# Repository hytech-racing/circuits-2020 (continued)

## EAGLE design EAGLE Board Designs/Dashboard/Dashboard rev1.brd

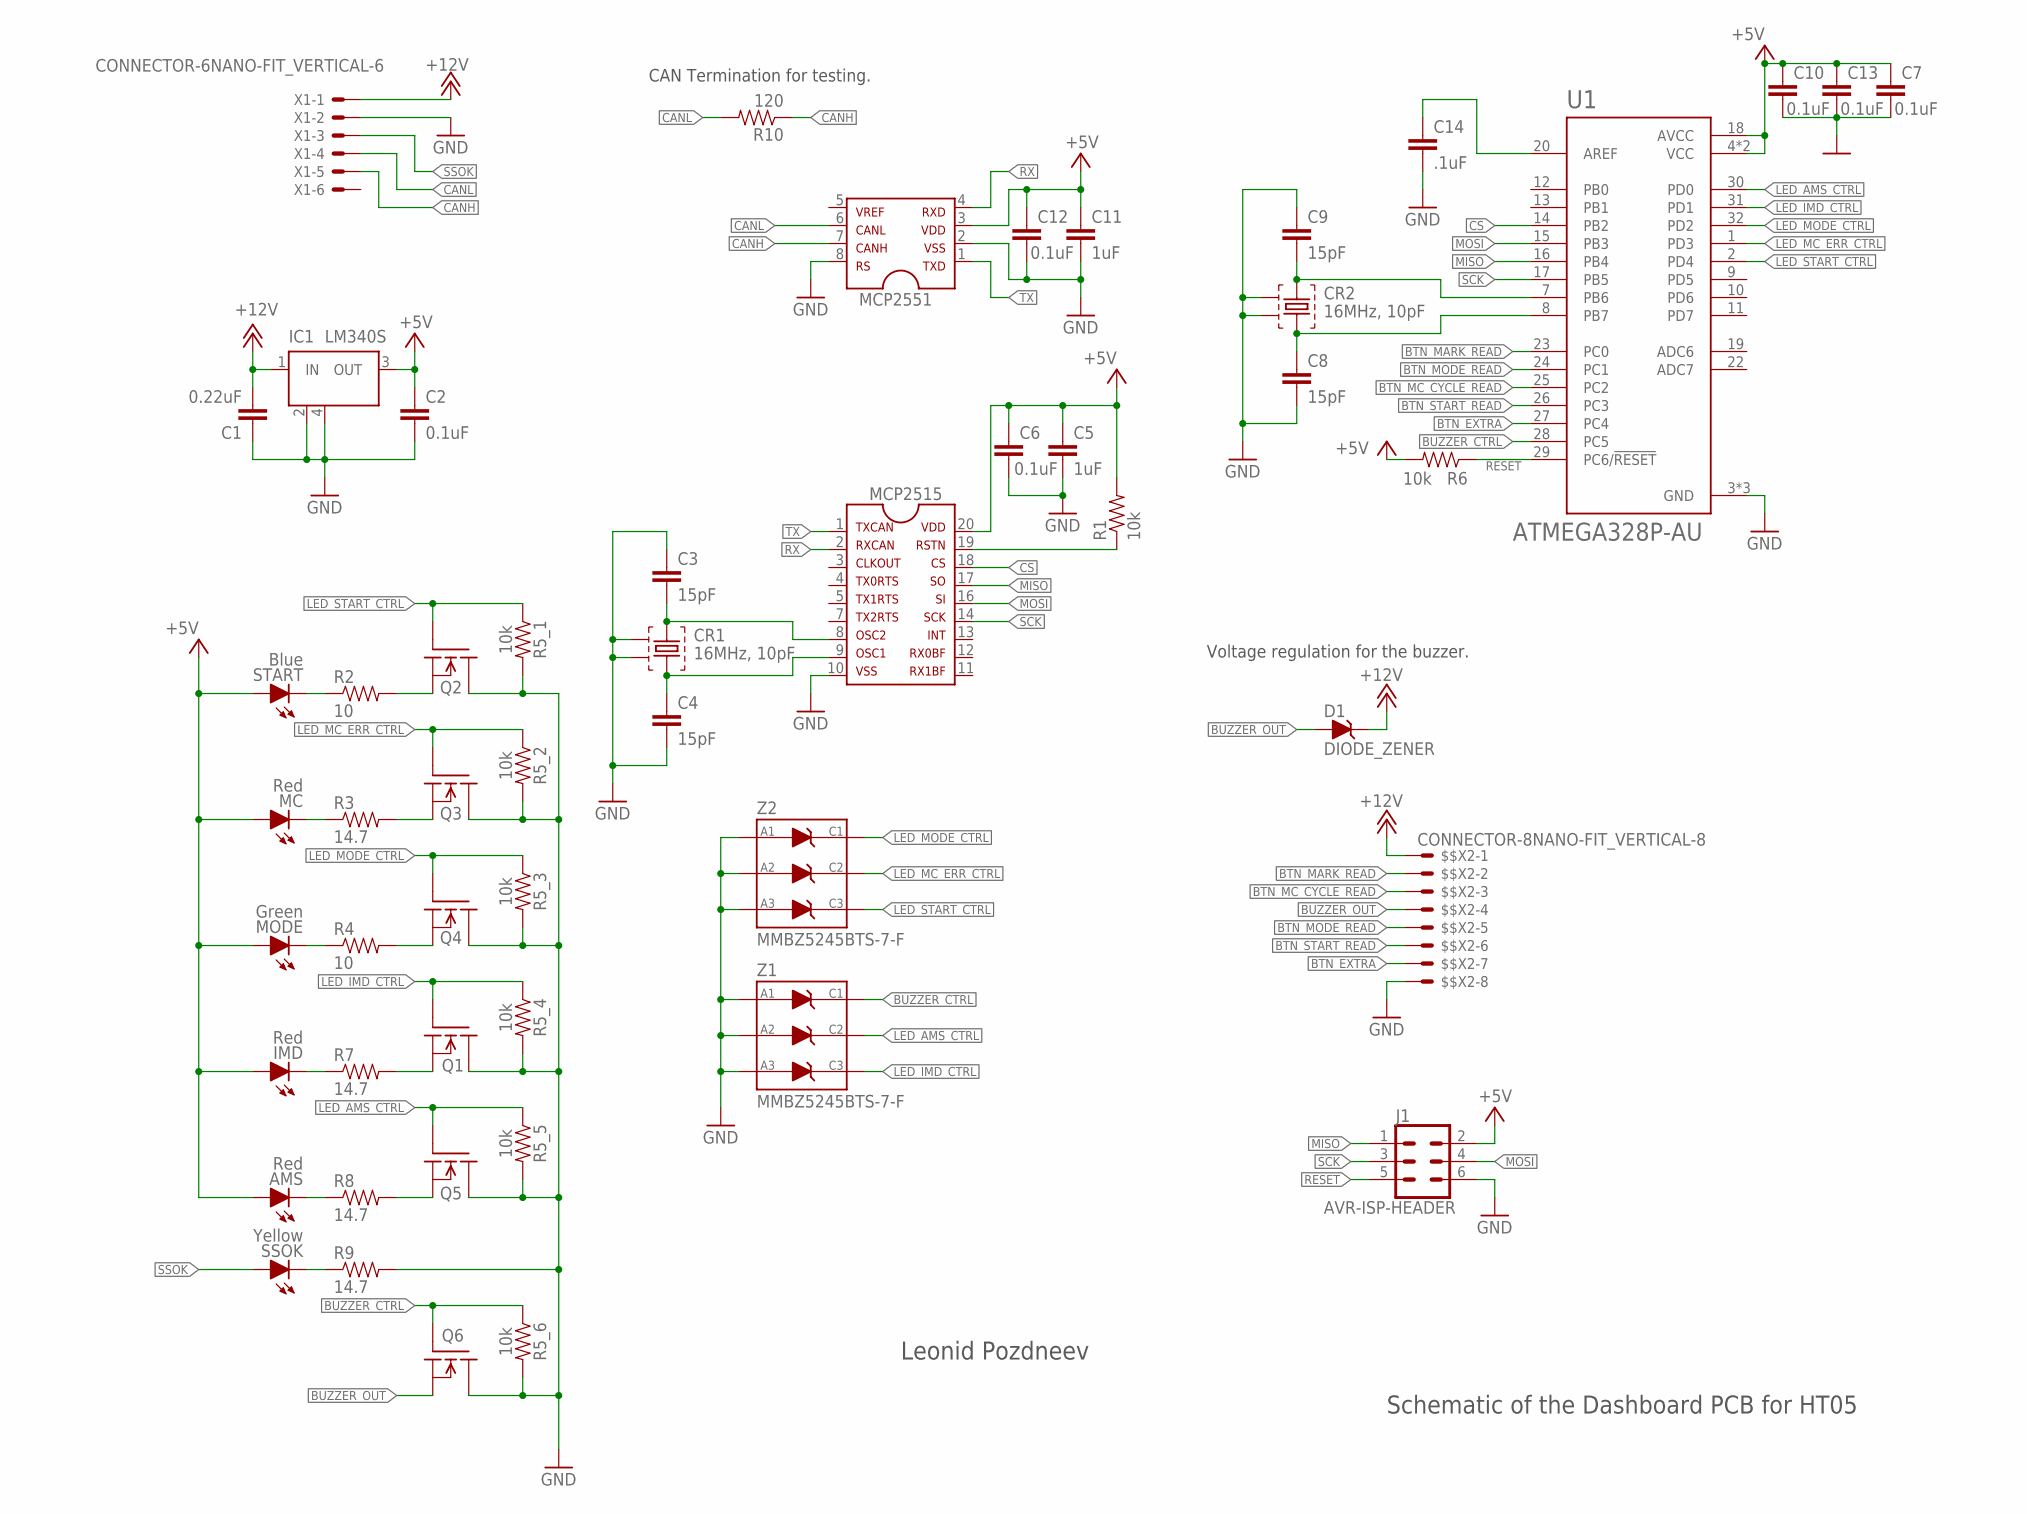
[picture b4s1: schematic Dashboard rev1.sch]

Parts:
$$X2: CONNECTOR-8NANO-FIT_VERTICAL-8; NANO-FIT_VERTICAL-8
AMS: Red; CREE_XP-E2
C1: 0.22uF; 0603-CAP
C2, C6, C7, C10, C12, C13: 0.1uF; 0603-CAP
C3, C4, C8, C9: 15pF; 0603-CAP
C5, C11: 1uF; 0603-CAP
C14: .1uF; 0603-CAP
CR1, CR2: 16MHz, 10pF; ABM3B
D1: DIODE_ZENER; SOT23
IC1: LM340S; SOT223
IMD: Red; CREE_XP-E2
J1: AVR-ISP-HEADER; 2X03
MC: Red; CREE_XP-E2
MCP2515: MCP2515TSSOP; TSSOP-20
MCP2551: MCP2551; SOIC-08
MODE: Green; CREE_XP-E2
Q1, Q2, Q3, Q4, Q5, Q6: DMG3406LSOT; SOT23
R1, R6: 10k; 0603-RES
R2, R4: 10; 0603-RES
R3, R7, R8, R9: 14.7; 0603-RES
R5: 10k; CAT16-*8
R10: 120; 0603-RES
SSOK: Yellow; CREE_XP-E2
START: Blue; CREE_XP-E2
U1: ATMEGA328P-AU; QFP80P900X900X120-32N
X1: CONNECTOR-6NANO-FIT_VERTICAL-6; NANO-FIT_VERTICAL-6
Z1, Z2: MMBZ5245BTS-7-F; SOT363

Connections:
+5V: AMS.P$1 (A), C2.1, C5.1, C6.1, C7.1, C10.1, C11.1, C12.1, C13.1, IC1.3 (OUT), IMD.P$1 (A), J1.2, MC.P$1 (A), MCP2515.20 (VDD), MCP2551.3, MODE.P$1 (A), R1.2, R6.2, START.P$1 (A), U1.4 (VCC), U1.6 (VCC), U1.18 (AVCC)
+12V: $$X2.P$1, C1.2, D1.3 (C), IC1.1 (IN), X1.P$1
BTN_EXTRA: $$X2.P$7, U1.27 (PC4)
BTN_MARK_READ: $$X2.P$2, U1.23 (PC0)
BTN_MC_CYCLE_READ: $$X2.P$3, U1.25 (PC2)
BTN_MODE_READ: $$X2.P$5, U1.24 (PC1)
BTN_START_READ: $$X2.P$6, U1.26 (PC3)
BUZZER_CTRL: Q6.1 (G), R5.P$6 (1), U1.28 (PC5), Z1.P$4 (C1)
BUZZER_OUT: $$X2.P$4, D1.1 (A), Q6.2 (S)
CANH: MCP2551.7, R10.1, X1.P$5
CANL: MCP2551.6, R10.2, X1.P$4
CS: MCP2515.18 (CS), U1.14 (PB2)
GND: $$X2.P$8, C1.1, C2.2, C3.1, C4.2, C5.2, C6.2, C7.2, C8.2, C9.1, C10.2, C11.2, C12.2, C13.2, C14.2, CR1.P$2 (2), CR1.P$4 (4), CR2.P$2 (2), CR2.P$4 (4), IC1.2 (GND), IC1.4 (GND), J1.6, MCP2515.10 (VSS), MCP2551.2, MCP2551.8, Q1.3 (D), Q2.3 (D), Q3.3 (D), Q4.3 (D), Q5.3 (D), Q6.3 (D), R5.P$11 (2), R5.P$12 (2), R5.P$13 (2), R5.P$14 (2), R5.P$15 (2), R5.P$16 (2), R9.2, U1.3 (GND), U1.5 (GND), U1.21 (GND), X1.P$2, Z1.P$1 (A1), Z1.P$2 (A2), Z1.P$3 (A3), Z2.P$1 (A1), Z2.P$2 (A2), Z2.P$3 (A3)
LED_AMS_CTRL: Q5.1 (G), R5.P$5 (1), U1.30 (PD0), Z1.P$5 (C2)
LED_IMD_CTRL: Q1.1 (G), R5.P$4 (1), U1.31 (PD1), Z1.P$6 (C3)
LED_MC_ERR_CTRL: Q3.1 (G), R5.P$2 (1), U1.1 (PD3), Z2.P$5 (C2)
LED_MODE_CTRL: Q4.1 (G), R5.P$3 (1), U1.32 (PD2), Z2.P$4 (C1)
LED_START_CTRL: Q2.1 (G), R5.P$1 (1), U1.2 (PD4), Z2.P$6 (C3)
MISO: J1.1, MCP2515.17 (SO), U1.16 (PB4)
MOSI: J1.4, MCP2515.16 (SI), U1.15 (PB3)
unnamed: MCP2515.19 (RSTN), R1.1
unnamed: C4.1, CR1.P$3 (3), MCP2515.9 (OSC1)
unnamed: C3.2, CR1.P$1 (1), MCP2515.8 (OSC2)
unnamed: Q2.2 (S), R2.2
unnamed: C9.2, CR2.P$1 (1), U1.7 (PB6)
unnamed: C8.1, CR2.P$3 (3), U1.8 (PB7)
unnamed: C14.1, U1.20 (AREF)
unnamed: Q4.2 (S), R4.2
unnamed: MODE.P$2 (C), R4.1
unnamed: R2.1, START.P$2 (C)
unnamed: Q1.2 (S), R7.2
unnamed: IMD.P$2 (C), R7.1
unnamed: R9.1, SSOK.P$2 (C)
unnamed: AMS.P$2 (C), R8.1
unnamed: Q5.2 (S), R8.2
unnamed: Q3.2 (S), R3.2
unnamed: MC.P$2 (C), R3.1
RESET: J1.5, R6.1, U1.29 (PC6/!RESET)
RX: MCP2515.2 (RXCAN), MCP2551.4
SCK: J1.3, MCP2515.14 (SCK), U1.17 (PB5)
SSOK: SSOK.P$1 (A), X1.P$3
TX: MCP2515.1 (TXCAN), MCP2551.1

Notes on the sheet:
Leonid Pozdneev
Schematic of the Dashboard PCB for HT05
Voltage regulation for the buzzer.
CAN Termination for testing.

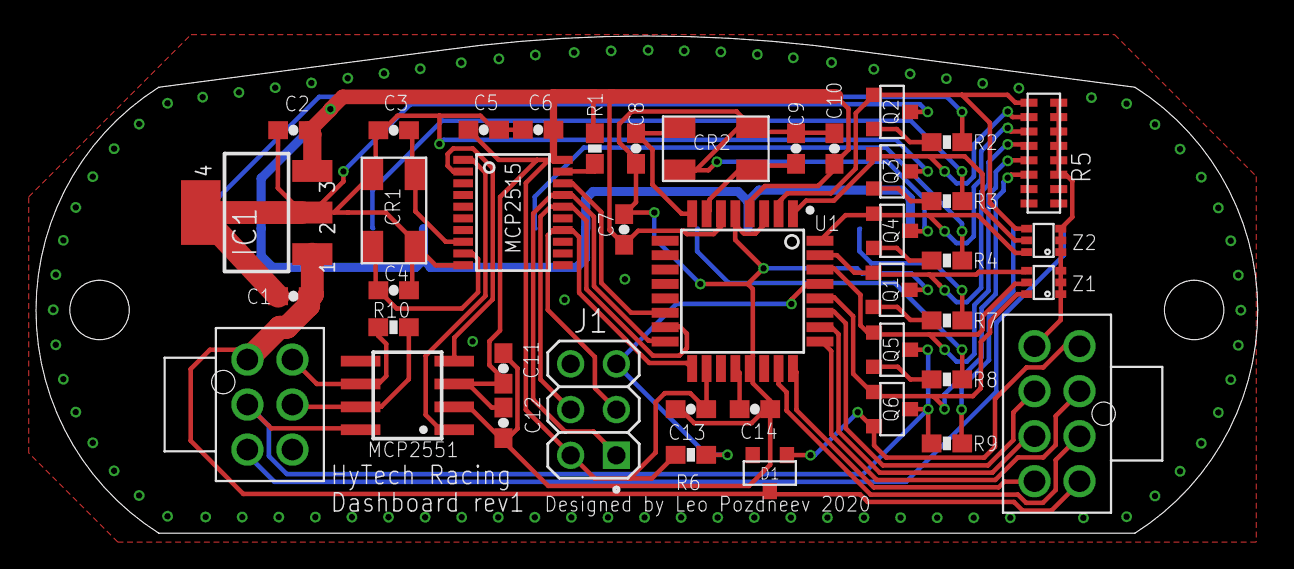
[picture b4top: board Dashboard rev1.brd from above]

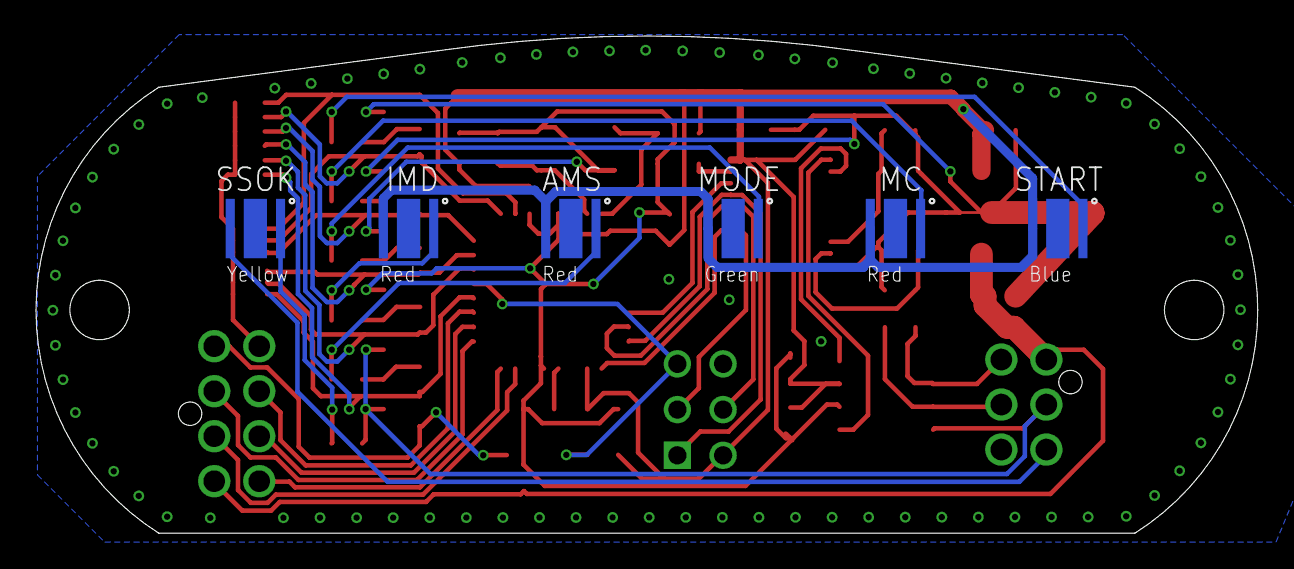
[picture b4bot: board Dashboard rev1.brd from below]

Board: 2 copper layers, 67.9 x 27.6 mm, 48 parts (6 on the bottom side), 42 nets.

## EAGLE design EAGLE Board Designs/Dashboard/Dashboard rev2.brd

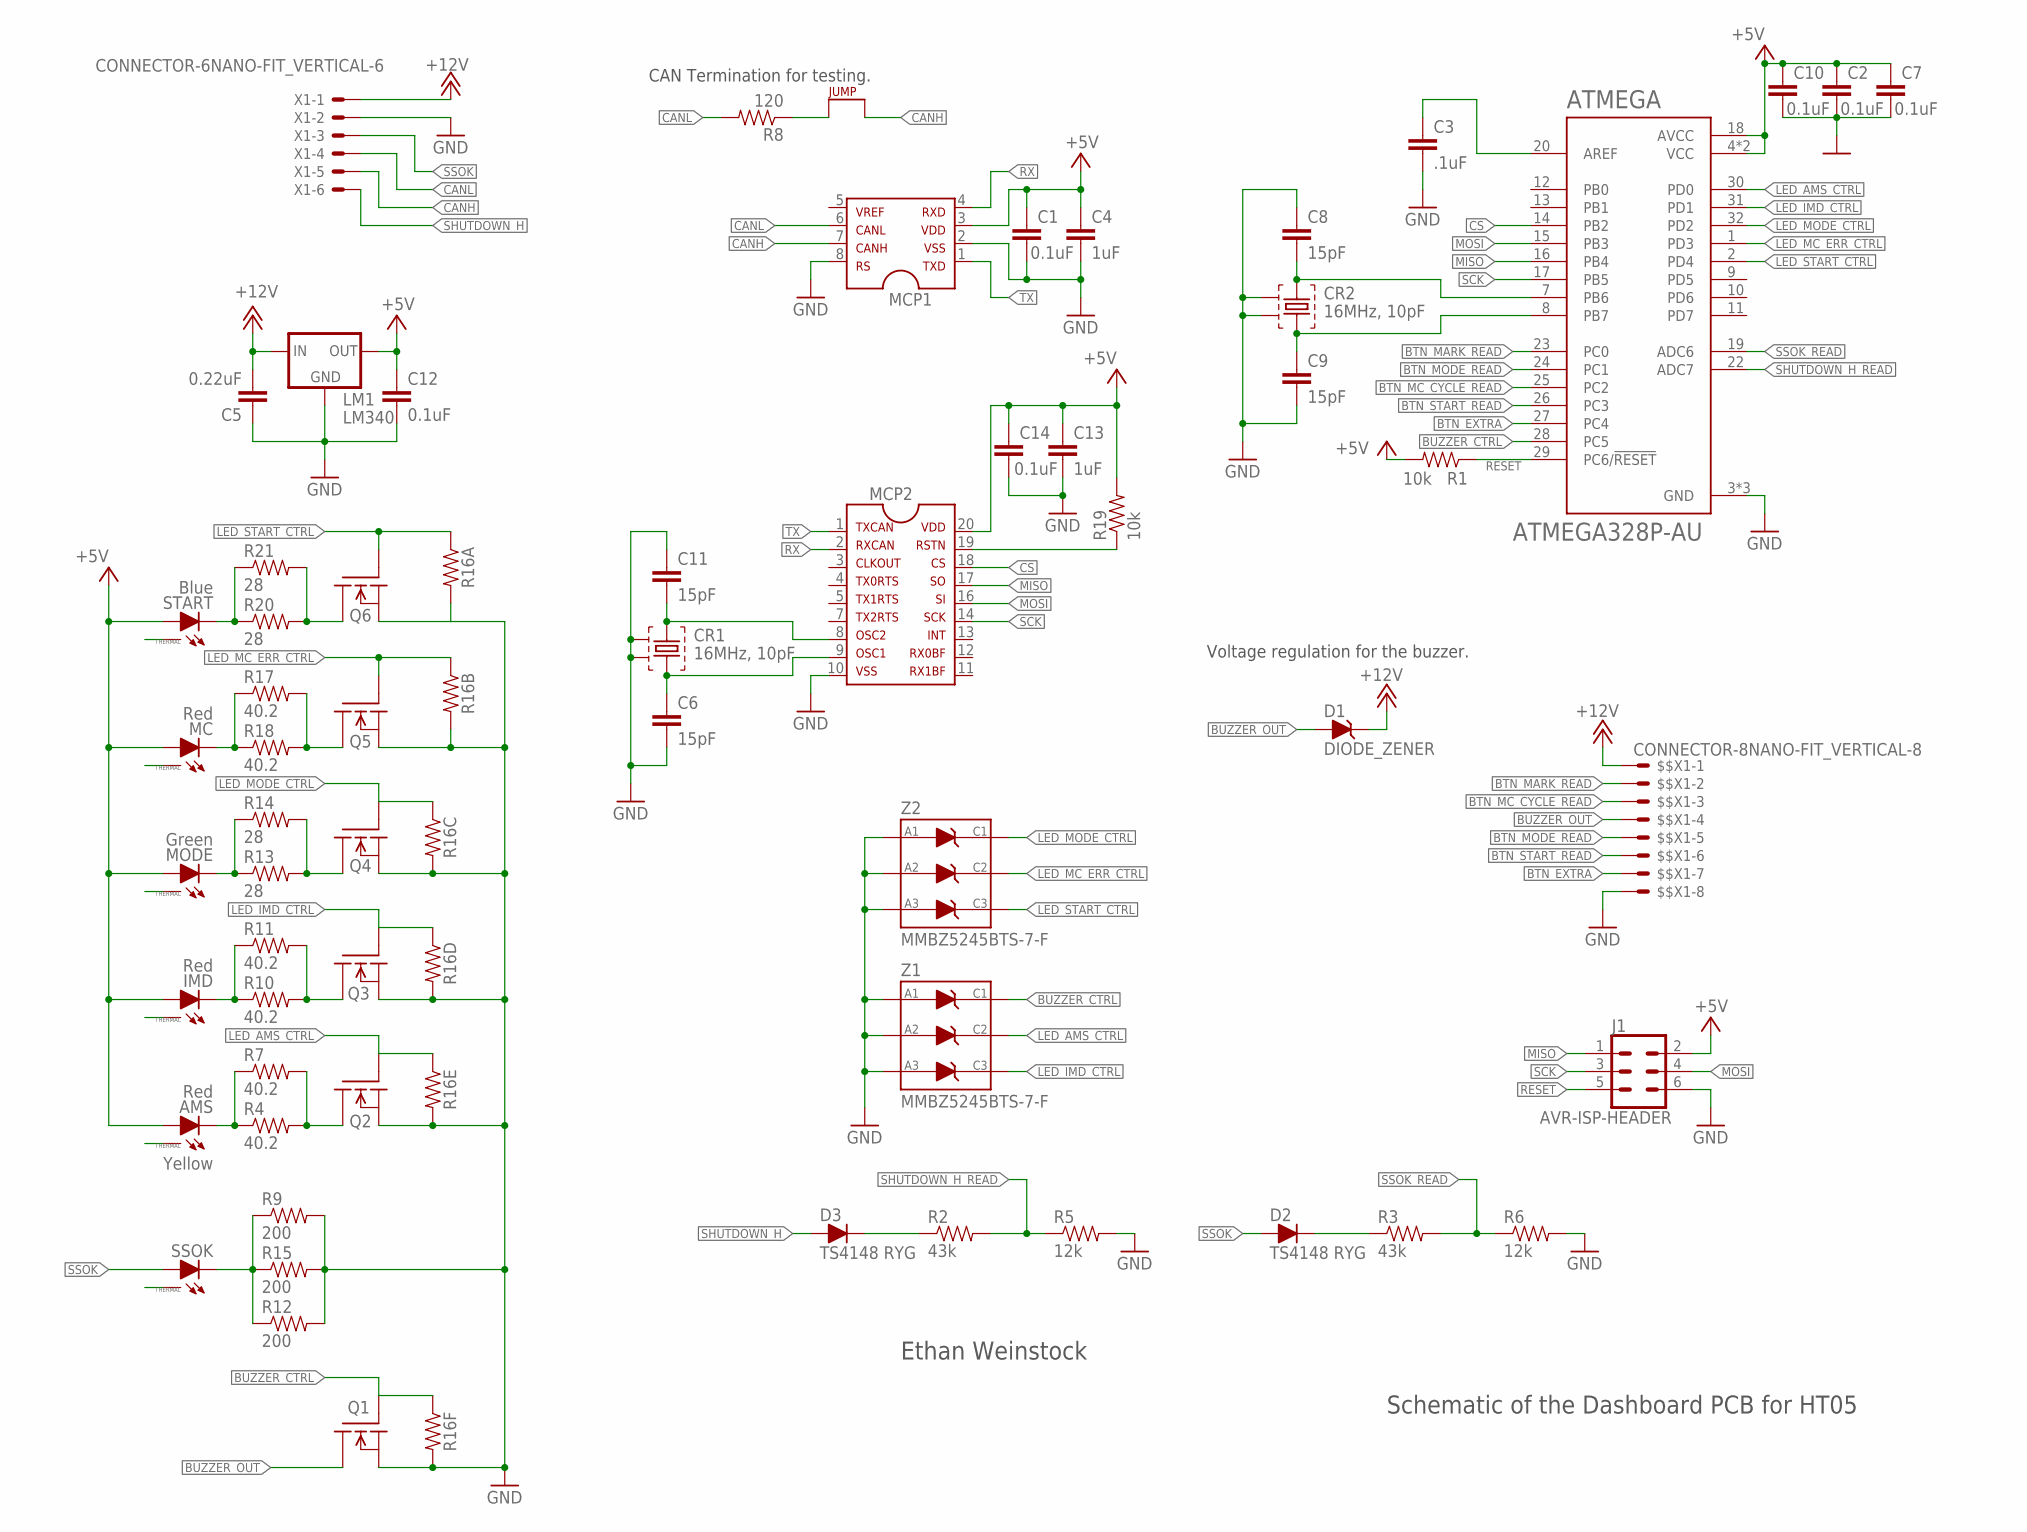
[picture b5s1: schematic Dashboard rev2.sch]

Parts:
$$X1: CONNECTOR-8NANO-FIT_VERTICAL-8; NANO-FIT_VERTICAL-8
AMS: Red; XP-E2
ATMEGA: ATMEGA328P-AU; QFP80P900X900X120-32N
C1, C2, C7, C10, C12, C14: 0.1uF; 0603-CAP
C3: .1uF; 0603-CAP
C4, C13: 1uF; 0603-CAP
C5: 0.22uF; 0603-CAP
C6, C8, C9, C11: 15pF; 0603-CAP
CR1, CR2: 16MHz, 10pF; ABM3B
D1: DIODE_ZENER; SOT23
D2, D3: TS4148 RYG; 0805_D
IMD: Red; XP-E2
J1: AVR-ISP-HEADER; 2X03
J2: JUMPER0603; 0603-JUMP
LM1: LM340; SOT223
MC: Red; XP-E2
MCP1: MCP2551; SOIC-08
MCP2: MCP2515TSSOP; TSSOP-20
MODE: Green; XP-E2
Q1, Q2, Q3, Q4, Q5, Q6: DMG3406LSOT; SOT23
R1, R19: 10k; 0603-RES
R2, R3: 43k; 0603-RES
R4, R7, R10, R11, R17, R18: 40.2; 0603-RES
R5, R6: 12k; 0603-RES
R8: 120; 0603-RES
R9, R12, R15: 200; 0805
R13, R14, R20, R21: 28; 0603-RES
R16: 10k; YAG_YC248-M
SSOK: Yellow; XP-E2
START: Blue; XP-E2
X1: CONNECTOR-6NANO-FIT_VERTICAL-6; NANO-FIT_VERTICAL-6
Z1, Z2: MMBZ5245BTS-7-F; SOT363

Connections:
+5V: AMS.A, ATMEGA.4 (VCC), ATMEGA.6 (VCC), ATMEGA.18 (AVCC), C1.1, C2.1, C4.1, C7.1, C10.1, C12.1, C13.1, C14.1, IMD.A, J1.2, LM1.3 (OUT), MC.A, MCP1.3, MCP2.20 (VDD), MODE.A, R1.2, R19.2, START.A
+12V: $$X1.P$1, C5.2, D1.3 (C), LM1.1 (IN), X1.P$1
BTN_EXTRA: $$X1.P$7, ATMEGA.27 (PC4)
BTN_MARK_READ: $$X1.P$2, ATMEGA.23 (PC0)
BTN_MC_CYCLE_READ: $$X1.P$3, ATMEGA.25 (PC2)
BTN_MODE_READ: $$X1.P$5, ATMEGA.24 (PC1)
BTN_START_READ: $$X1.P$6, ATMEGA.26 (PC3)
BUZZER_CTRL: ATMEGA.28 (PC5), Q1.1 (G), R16.6 (1), Z1.P$4 (C1)
BUZZER_OUT: $$X1.P$4, D1.1 (A), Q1.3 (D)
CANH: J2.2, MCP1.7, X1.P$5
CANL: MCP1.6, R8.2, X1.P$4
CS: ATMEGA.14 (PB2), MCP2.18 (CS)
GND: $$X1.P$8, ATMEGA.3 (GND), ATMEGA.5 (GND), ATMEGA.21 (GND), C1.2, C2.2, C3.2, C4.2, C5.1, C6.2, C7.2, C8.1, C9.2, C10.2, C11.1, C12.2, C13.2, C14.2, CR1.GND, CR1.GND2, CR2.GND, CR2.GND2, J1.6, LM1.2 (GND), LM1.4 (GND), MCP1.2, MCP1.8, MCP2.10 (VSS), Q1.2 (S), Q2.2 (S), Q3.2 (S), Q4.2 (S), Q5.2 (S), Q6.2 (S), R5.2, R6.2, R9.2, R12.2, R15.2, R16.11 (2), R16.12 (2), R16.13 (2), R16.14 (2), R16.15 (2), R16.16 (2), X1.P$2, Z1.P$1 (A1), Z1.P$2 (A2), Z1.P$3 (A3), Z2.P$1 (A1), Z2.P$2 (A2), Z2.P$3 (A3)
LED_AMS_CTRL: ATMEGA.30 (PD0), Q2.1 (G), R16.5 (1), Z1.P$5 (C2)
LED_IMD_CTRL: ATMEGA.31 (PD1), Q3.1 (G), R16.4 (1), Z1.P$6 (C3)
LED_MC_ERR_CTRL: ATMEGA.1 (PD3), Q5.1 (G), R16.2 (1), Z2.P$5 (C2)
LED_MODE_CTRL: ATMEGA.32 (PD2), Q4.1 (G), R16.3 (1), Z2.P$4 (C1)
LED_START_CTRL: ATMEGA.2 (PD4), Q6.1 (G), R16.1, Z2.P$6 (C3)
MISO: ATMEGA.16 (PB4), J1.1, MCP2.17 (SO)
MOSI: ATMEGA.15 (PB3), J1.4, MCP2.16 (SI)
unnamed: MCP2.19 (RSTN), R19.1
unnamed: C6.1, CR1.3, MCP2.9 (OSC1)
unnamed: C11.2, CR1.1, MCP2.8 (OSC2)
unnamed: Q6.3 (D), R20.2, R21.2
unnamed: ATMEGA.7 (PB6), C8.2, CR2.1
unnamed: ATMEGA.8 (PB7), C9.1, CR2.3
unnamed: D2.C, R3.1
unnamed: ATMEGA.20 (AREF), C3.1
unnamed: Q5.3 (D), R17.2, R18.2
unnamed: MODE.C, R13.1, R14.1
unnamed: R20.1, R21.1, START.C
unnamed: Q4.3 (D), R13.2, R14.2
unnamed: IMD.C, R10.1, R11.1
unnamed: D3.C, R2.1
unnamed: R9.1, R12.1, R15.1, SSOK.C
unnamed: AMS.C, R4.1, R7.1
unnamed: Q3.3 (D), R10.2, R11.2
unnamed: Q2.3 (D), R4.2, R7.2
unnamed: MC.C, R17.1, R18.1
unnamed: J2.1, R8.1
RESET: ATMEGA.29 (PC6/!RESET), J1.5, R1.1
RX: MCP1.4, MCP2.2 (RXCAN)
SCK: ATMEGA.17 (PB5), J1.3, MCP2.14 (SCK)
SHUTDOWN_H: D3.A, X1.P$6
SHUTDOWN_H_READ: ATMEGA.22 (ADC7), R2.2, R5.1
SSOK: D2.A, SSOK.A, X1.P$3
SSOK_READ: ATMEGA.19 (ADC6), R3.2, R6.1
THERMAL: AMS.X, IMD.X, MC.X, MODE.X, SSOK.X, START.X
TX: MCP1.1, MCP2.1 (TXCAN)

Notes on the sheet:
Ethan Weinstock
Schematic of the Dashboard PCB for HT05
Voltage regulation for the buzzer.
CAN Termination for testing.

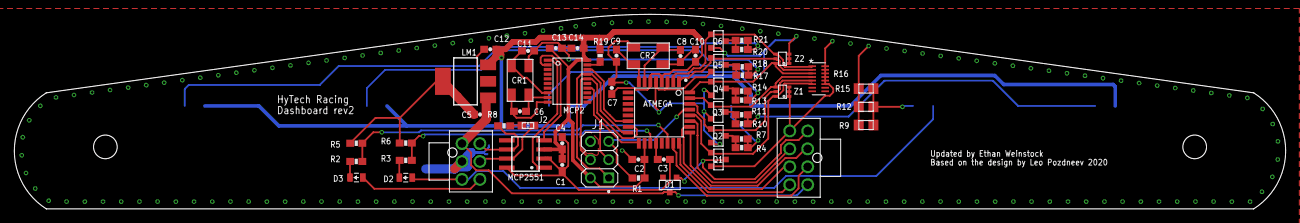
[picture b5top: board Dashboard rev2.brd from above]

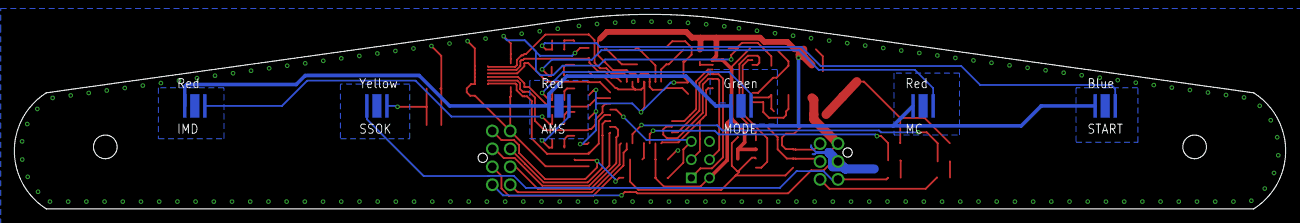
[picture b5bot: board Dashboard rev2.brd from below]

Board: 2 copper layers, 177.4 x 27.1 mm, 62 parts (6 on the bottom side), 49 nets.
